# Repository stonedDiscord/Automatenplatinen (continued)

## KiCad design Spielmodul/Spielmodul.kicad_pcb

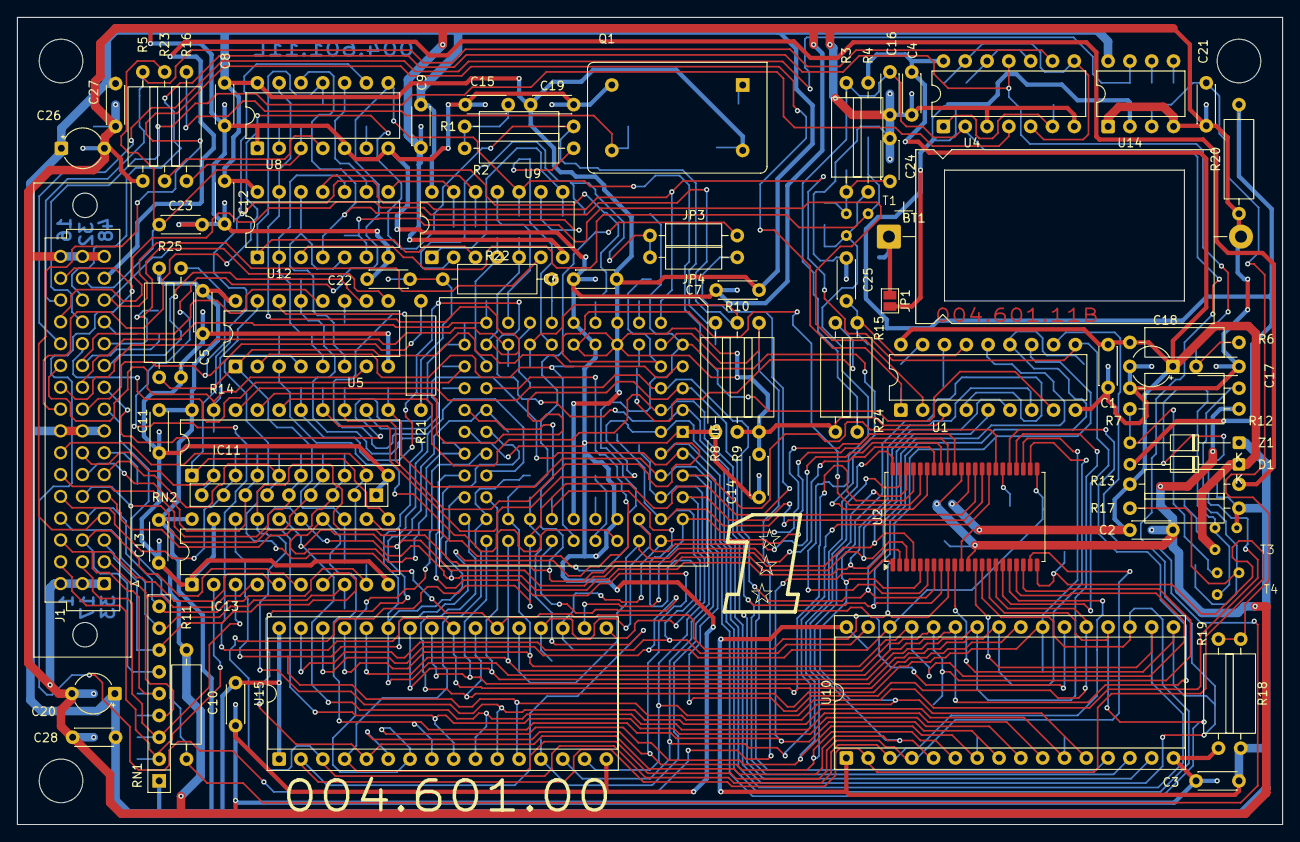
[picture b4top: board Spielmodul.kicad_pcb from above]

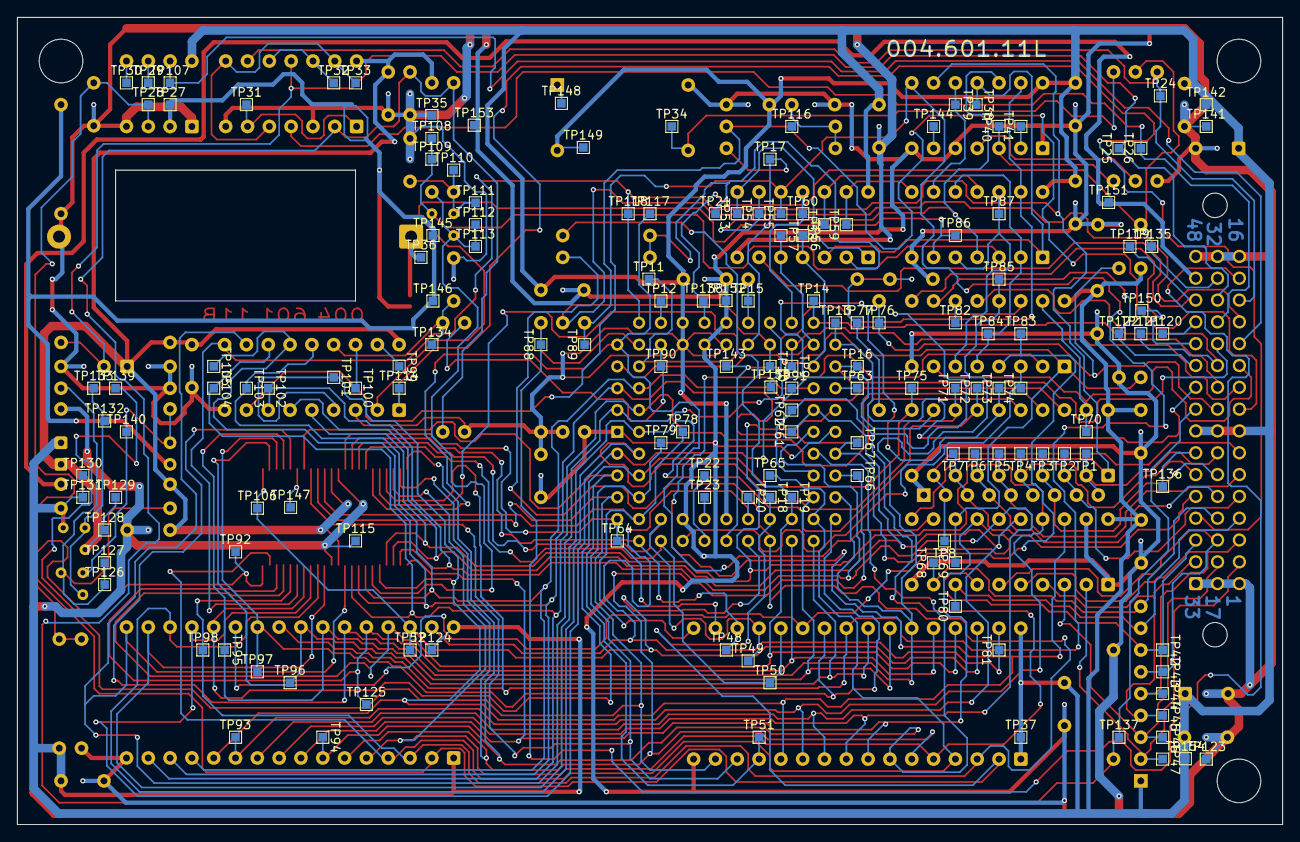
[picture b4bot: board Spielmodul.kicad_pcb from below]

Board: 2 copper layers, 147.3 x 94.0 mm, 234 parts (155 on the bottom side), 130 nets.

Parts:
BT1: Battery_Cell; CP_Axial_L34.5mm_D20.0mm_P41.00mm_Horizontal
C1, C2, C3, C4, C5, C6, C7, C8, C9, C10, C11, C12, C13, C14, C19, C21, C27, C28: 104M; C_Disc_D4.3mm_W1.9mm_P5.00mm
C15, C16, C22, C25: 470K; C_Disc_D4.3mm_W1.9mm_P5.00mm
C17: 103; C_Disc_D4.3mm_W1.9mm_P5.00mm
C18: 2u2 35; CP_Radial_Tantal_D4.5mm_P5.00mm
C20, C26: 10u 16; CP_Radial_Tantal_D4.5mm_P5.00mm
C23, C24: C; C_Disc_D4.3mm_W1.9mm_P5.00mm
D1: D; D_DO-34_SOD68_P12.70mm_Horizontal
IC11, IC13: 74HC245; DIP-20_W7.62mm
J1: DIN41612_03x16_ABC; DIN41612_R2_3x16_Male_Vertical_THT
JP1: Jumper_2_Open; SolderJumper-2_P1.3mm_Open_Pad1.0x1.5mm
JP3: Jumper_2_Bridged; R_Axial_DIN0207_L6.3mm_D2.5mm_P10.16mm_Horizontal
JP4: Jumper_2_Open; R_Axial_DIN0207_L6.3mm_D2.5mm_P10.16mm_Horizontal
Q1: ACO-xxxMHz; Oscillator_DIP-14
R1, R2, R7, R16, R21, R22, R23, R24: 100; R_Axial_DIN0309_L9.0mm_D3.2mm_P12.70mm_Horizontal
R3: 330; R_Axial_DIN0309_L9.0mm_D3.2mm_P12.70mm_Horizontal
R4, R15: 1k; R_Axial_DIN0309_L9.0mm_D3.2mm_P12.70mm_Horizontal
R5, R8, R13, R14, R25: 47k; R_Axial_DIN0309_L9.0mm_D3.2mm_P12.70mm_Horizontal
R6: 2.2M; R_Axial_DIN0309_L9.0mm_D3.2mm_P12.70mm_Horizontal
R9, R11: 10k; R_Axial_DIN0309_L9.0mm_D3.2mm_P12.70mm_Horizontal
R10: 4,7k; R_Axial_DIN0309_L9.0mm_D3.2mm_P12.70mm_Horizontal
R12: 47; R_Axial_DIN0309_L9.0mm_D3.2mm_P12.70mm_Horizontal
R17: 470; R_Axial_DIN0309_L9.0mm_D3.2mm_P12.70mm_Horizontal
R18: 56k; R_Axial_DIN0309_L9.0mm_D3.2mm_P12.70mm_Horizontal
R19: 39k; R_Axial_DIN0309_L9.0mm_D3.2mm_P12.70mm_Horizontal
R20: 10M; R_Axial_DIN0309_L9.0mm_D3.2mm_P12.70mm_Horizontal
RN1, RN2: R_Network08; R_Array_SIP9
T1: BS170; TO92
T3: BC557; TO92
T4: BC546; TO92
TP1, TP2, TP3, TP4, TP5, TP6, TP7, TP8: TestPoint; TestPoint_Pad_1.0x1.0mm
TP9: IPL2; TestPoint_Pad_1.0x1.0mm
TP10: VPA; TestPoint_Pad_1.0x1.0mm
TP11: UDS; TestPoint_Pad_1.0x1.0mm
TP12: BG; TestPoint_Pad_1.0x1.0mm
TP13: IPL0; TestPoint_Pad_1.0x1.0mm
TP14: IPL1; TestPoint_Pad_1.0x1.0mm
TP15, TP77: HALT; TestPoint_Pad_1.0x1.0mm
TP16, TP18, TP19, TP20, TP22, TP23, TP31, TP32, TP33, TP35, TP37, TP38, TP39, TP40, TP41, TP42, TP43, TP44, TP45, TP46, TP47, TP48, TP49, TP50, TP51, TP52, TP53, TP54, TP55, TP56, TP57, TP58, TP59, TP60, TP61, TP62, TP63, TP64, TP65, TP66, TP67, TP68, TP69, TP70, TP71, TP72, TP73, TP74, TP75, TP76, TP78, TP79, TP80, TP81, TP82, TP83, TP84, TP85, TP86, TP87, TP88, TP89, TP91, TP92, TP93, TP94, TP95, TP96, TP97, TP98, TP99, TP100, TP101, TP102, TP103, TP104, TP105, TP106, TP107, TP108, TP109, TP110, TP111, TP112, TP113, TP114, TP115, TP119, TP134, TP135, TP139, TP140, TP143, TP144, TP145, TP146, TP147, TP155: TestPoint_Pad_1.0x1.0mm
TP17, TP116: RESET; TestPoint_Pad_1.0x1.0mm
TP21: TP; TestPoint_Pad_1.0x1.0mm
TP24: c_c14; TestPoint_Pad_1.0x1.0mm
TP25: c_b14; TestPoint_Pad_1.0x1.0mm
TP26, TP120, TP121, TP122, TP123, TP124, TP125, TP126, TP127, TP128, TP129, TP130, TP131, TP132, TP133, TP136, TP137, TP141, TP142, TP148, TP149, TP150, TP151, TP152, TP153, TP154: c_b13; TestPoint_Pad_1.0x1.0mm
TP27: +BATT; TestPoint_Pad_1.0x1.0mm
TP28: MINUS; TestPoint_Pad_1.0x1.0mm
TP29: STRB; TestPoint_Pad_1.0x1.0mm
TP30: BAL; TestPoint_Pad_1.0x1.0mm
TP34: CLOCK_OUT; TestPoint_Pad_1.0x1.0mm
TP36: BT+; TestPoint_Pad_1.0x1.0mm
TP90: BGACK; TestPoint_Pad_1.0x1.0mm
TP117: LDS; TestPoint_Pad_1.0x1.0mm
TP118: RW; TestPoint_Pad_1.0x1.0mm
TP138: CLK; TestPoint_Pad_1.0x1.0mm
U1: RTC72421; DIP-18_W7.62mm
U2: K6T4016C3C; TSOP-II-44_10.16x18.41mm_P0.8mm
U4: 74HC02; DIP-14_W7.62mm
U5: 74HC139; DIP-16_W7.62mm
U6: MC68EC000FN16; PLCC-68_THT-Socket
U8: 74HC14; DIP-14_W7.62mm
U9: 74HC08; DIP-14_W7.62mm
U10, U15: 27C040; DIP-32_W15.24mm_Socket
U12: 74HC32; DIP-14_W7.62mm
U14: LM311; DIP-8_W7.62mm
Z1: D_Zener; D_DO-34_SOD68_P12.70mm_Horizontal

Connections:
+BATT: D1.2 (A), JP1.2 (B), R20.2, TP27.1 (1_1), TP145.1 (1_1), TP146.1 (1_1), U14.2 (+)
/cA1: IC13.2 (A0), J1.c2, RN1.2 (R1), TP47.1 (1_1)
/cA2: IC13.3 (A1), J1.b2, RN1.3 (R2), TP46.1 (1_1)
/cA3: IC13.4 (A2), J1.a2, RN1.4 (R3), TP45.1 (1_1)
/cA4: IC13.5 (A3), J1.c3, RN1.5 (R4), TP44.1 (1_1)
/cA5: IC13.6 (A4), J1.b3, RN1.6 (R5), TP43.1 (1_1)
/cAS: IC13.7 (A5), J1.a3, RN1.7 (R6), TP42.1 (1_1)
/cD0: IC11.2 (A0), J1.b7, RN2.9 (R8), TP1.1 (1_1)
/cD1: IC11.3 (A1), J1.c5, RN2.8 (R7), TP2.1 (1_1)
/cD2: IC11.4 (A2), J1.b6, RN2.7 (R6), TP3.1 (1_1)
/cD3: IC11.5 (A3), J1.a6, RN2.6 (R5), TP4.1 (1_1)
/cD4: IC11.6 (A4), J1.c6, RN2.5 (R4), TP5.1 (1_1)
/cD5: IC11.7 (A5), J1.b5, RN2.4 (R3), TP6.1 (1_1)
/cD6: IC11.8 (A6), J1.a5, RN2.3 (R2), TP7.1 (1_1)
/cD7: IC11.9 (A7), J1.c7, RN2.2 (R1), TP8.1 (1_1)
/cHALT: J1.b9, R14.2, R21.2, TP76.1 (1_1)
/cLDS: IC13.8 (A6), J1.c4, RN1.8 (R7), TP80.1 (1_1)
/cRAMVCC: J1.a15, R13.2, TP151.1 (1_1)
/cRESET: J1.c9, R1.2, R8.2, TP89.1 (1_1)
/cRW: IC13.9 (A7), J1.b4, RN1.9 (R8), TP68.1 (1_1)
/c_a4: J1.a4, TP114.1 (1_1), U1.1 (STD.P)
/c_a7: J1.a7, TP136.1 (1_1)
/c_a9: C16.1, J1.a9, R3.2, R11.1, R24.1, TP137.1 (1_1), U4.2
/c_a11: J1.a11, TP122.1 (1_1), U5.10 (O2)
/c_a12: J1.a12, TP150.1 (1_1), U5.9 (O3)
/c_a13: J1.a13, TP120.1 (1_1)
/c_b11: J1.b11, TP121.1 (1_1), U5.12 (O0)
/c_b13: J1.b13, TP26.1 (1_1), U4.4
/c_b14: C17.1, J1.b14, R6.2, TP25.1 (1_1), U4.11
/c_c12: J1.c12, TP107.1 (1_1), U14.7
/c_c14: J1.c14, R5.2, TP24.1 (1_1), U4.9
/c~USER: J1.a14, TP119.1 (1_1), U9.6
A0: TP63.1 (1_1), U6.31 (A0)
A1: IC13.18 (B0), TP101.1 (1_1), U1.4 (A0), U2.5 (A0), U6.32 (A1), U10.12 (A0), U15.12 (A0)
A2: IC13.17 (B1), TP93.1 (1_1), U1.5 (A1), U2.4 (A1), U6.33 (A2), U10.11 (A1), U15.11 (A1)
A3: IC13.16 (B2), TP61.1 (1_1), U1.6 (A2), U2.3 (A2), U6.34 (A3), U10.10 (A2), U15.10 (A2)
A4: IC13.15 (B3), TP102.1 (1_1), U1.7 (A3), U2.2 (A3), U6.36 (A4), U10.9 (A3), U15.9 (A3)
A5: IC13.14 (B4), TP67.1 (1_1), U2.1 (A4), U6.37 (A5), U10.8 (A4), U15.8 (A4)
A6: TP94.1 (1_1), U2.44 (A5), U6.38 (A6), U10.7 (A5), U15.7 (A5)
A7: TP66.1 (1_1), U2.43 (A6), U6.39 (A7), U10.6 (A6), U15.6 (A6)
A8: TP62.1 (1_1), U2.42 (A7), U5.14 (A0), U6.40 (A8), U10.5 (A7), U15.5 (A7)
A9: TP85.1 (1_1), U2.27 (A8), U5.13 (A1), U6.41 (A9), U10.27 (A8), U15.27 (A8)
A10: TP95.1 (1_1), U2.26 (A9), U6.42 (A10), U10.26 (A9), U15.26 (A9)
A11: TP97.1 (1_1), U2.25 (A10), U6.43 (A11), U10.23 (A10), U15.23 (A10)
A12: TP96.1 (1_1), U2.24 (A11), U6.44 (A12), U10.25 (A11), U15.25 (A11)
A13: TP65.1 (1_1), U2.21 (A14), U6.45 (A13), U10.4 (A12), U15.4 (A12)
A14: TP125.1 (1_1), U2.20 (A15), U6.46 (A14), U10.28 (A13), U15.28 (A13)
A15: JP3.2 (B), TP19.1 (1_1), U2.19 (A16), U6.47 (A15), U10.29 (A14), U15.29 (A14)
A16: JP4.2 (B), TP98.1 (1_1), U2.18 (A17), U6.48 (A16), U10.3 (A15), U15.3 (A15)
A17: TP18.1 (1_1), TP92.1 (1_1), U2.22 (A13), U6.49 (A17), U10.2 (A16), U15.2 (A16)
A18: TP52.1 (1_1), TP106.1 (1_1), U2.23 (A12), U6.50 (A18), U10.30 (A17), U15.30 (A17)
A19: TP20.1 (1_1), TP81.1 (1_1), U6.51 (A19), U10.31 (A18), U15.31 (A18)
A20: TP143.1 (1_1), U5.2 (A0), U6.52 (A20)
A21: TP22.1 (1_1), U6.54 (A21)
A22: TP23.1 (1_1), U6.55 (A22)
A23: TP74.1 (1_1), U5.3 (A1), U6.56 (A23)
AS: IC13.13 (B5), R25.1, TP69.1 (1_1), U5.1 (E), U6.7 (~AS)
CLK: C23.1, J1.b15, R23.2, TP135.1 (1_1), TP138.1 (1_1), U6.16 (CLK)
D0: IC11.18 (B0), TP103.1 (1_1), U1.14 (D0), U2.7 (I/O1), U6.6 (D0), U10.13 (D0)
D1: IC11.17 (B1), TP105.1 (1_1), U1.13 (D1), U2.8 (I/O2), U6.5 (D1), U10.14 (D1)
D2: IC11.16 (B2), TP104.1 (1_1), U1.12 (D2), U2.9 (I/O3), U6.4 (D2), U10.15 (D2)
D3: IC11.15 (B3), TP73.1 (1_1), U1.11 (D3), U2.10 (I/O4), U6.3 (D3), U10.17 (D3)
D4: IC11.14 (B4), TP72.1 (1_1), U2.13 (I/O5), U6.2 (D4), U10.18 (D4)
D5: IC11.13 (B5), TP71.1 (1_1), U2.14 (I/O6), U6.68 (D5), U10.19 (D5)
D6: IC11.12 (B6), TP91.1 (1_1), U2.15 (I/O7), U6.67 (D6), U10.20 (D6)
D7: IC11.11 (B7), TP75.1 (1_1), U2.16 (I/O8), U6.66 (D7), U10.21 (D7)
D8: TP51.1 (1_1), U2.29 (I/O9), U6.65 (D8), U15.13 (D0)
D9: TP79.1 (1_1), U2.30 (I/O10), U6.64 (D9), U15.14 (D1)
D10: TP139.1 (1_1), U2.31 (I/O11), U6.63 (D10), U15.15 (D2)
D11: TP78.1 (1_1), U2.32 (I/O12), U6.62 (D11), U15.17 (D3)
D12: TP64.1 (1_1), U2.35 (I/O13), U6.61 (D12), U15.18 (D4)
D13: TP48.1 (1_1), U2.36 (I/O14), U6.60 (D13), U15.19 (D5)
D14: TP49.1 (1_1), U2.37 (I/O15), U6.59 (D14), U15.20 (D6)
D15: TP50.1 (1_1), U2.38 (I/O16), U6.58 (D15), U15.21 (D7)
EXT_RANGE: IC11.19 (CE), J1.c11, TP70.1 (1_1), U5.7 (O3), U5.15 (E)
FC0: TP56.1 (1_1), U6.30 (FC0), U9.4
FC1: J1.b12, TP16.1 (1_1), U6.29 (FC1)
FC2: TP57.1 (1_1), U6.28 (FC2), U8.13, U9.5, U12.13
GND: BT1.2 (-), C1.2, C2.2, C3.2, C4.2, C5.2, C6.2, C7.2, C8.2, C9.2, C10.2, C11.2, C12.2, C13.2, C14.2, C15.2, C16.2, C17.2, C18.2, C19.2, C20.2, C21.2, C22.2, C23.2, C24.2, C25.2, C26.2, C27.2, C28.2, IC11.10 (GND), IC13.1 (A->B), IC13.10 (GND), IC13.19 (CE), J1.a1, J1.a16, J1.b1, J1.b16, J1.c1, J1.c16, Q1.7 (GND), R5.1, R7.2, R8.1, R11.2, R12.1, R14.1, R19.1, R20.1, RN2.1 (common), TP35.1 (1_1), TP115.1 (1_1), TP123.1 (1_1), TP141.1 (1_1), TP152.1 (1_1), TP153.1 (1_1), U1.9 (GND), U2.12 (Vss), U2.34 (Vss), U4.3, U4.7 (GND), U5.8 (GND), U6.1 (GND), U6.17 (GND), U6.18 (GND), U6.35 (GND), U6.57 (GND), U8.1, U8.5, U8.7 (GND), U9.7 (GND), U10.16 (GND), U12.7 (GND), U14.1 (GND), U14.4 (V-), U15.16 (GND)
IPL0: J1.a10, TP13.1 (1_1), U6.27 (~IPL0)
IPL1: J1.b10, TP14.1 (1_1), U6.26 (~IPL1)
IPL2: J1.c10, TP9.1 (1_1), U6.25 (~IPL2)
LDS: IC13.12 (B6), TP117.1 (1_1), U2.39 (~LB), U6.9 (~LDS)
unnamed: BT1.1 (+), JP1.1 (A), TP36.1 (1_1)
unnamed: C15.1, R1.1, R2.1, TP116.1 (1_1)
unnamed: C22.1, R21.1, R22.1, TP77.1 (1_1)
unnamed: JP3.1 (A), JP4.1 (A), TP21.1 (1_1), U9.2
unnamed: Q1.8 (OUT), R16.2, TP34.1 (1_1)
unnamed: R16.1, TP40.1 (1_1), U8.3
unnamed: R23.1, U8.4
unnamed: R4.1, T1.1 (D), TP112.1 (1_1), TP113.1 (1_1), U2.6 (~CS)
unnamed: C24.1, R3.1, T1.2 (G), TP110.1 (1_1), TP111.1 (1_1)
unnamed: T3.2 (B), T4.1 (C), TP132.1 (1_1), TP133.1 (1_1)
unnamed: R7.1, T4.2 (B), TP140.1 (1_1), Z1.2 (A)
unnamed: R12.2, R17.1, T4.3 (E), TP126.1 (1_1), TP127.1 (1_1)
unnamed: TP31.1 (1_1), U4.1, U4.6
unnamed: TP32.1 (1_1), U4.10, U4.12
unnamed: TP33.1 (1_1), U4.5, U4.8, U4.13
unnamed: TP38.1 (1_1), U8.11, U9.3, U12.1
unnamed: TP39.1 (1_1), U8.10, U12.9
unnamed: TP41.1 (1_1), U8.2
unnamed: TP53.1 (1_1), U9.1, U9.8
unnamed: TP54.1 (1_1), U8.12, U9.9, U12.4
unnamed: TP58.1 (1_1), U9.12, U12.11
unnamed: TP59.1 (1_1), U9.13, U12.8
unnamed: TP99.1 (1_1), U1.17 (Vdd)
unnamed: TP100.1 (1_1), U1.16 (Vdd)
unnamed: TP144.1 (1_1), U8.6
unnamed: C25.1, R24.2, TP134.1 (1_1), U1.15 (CS1)
unnamed: TP82.1 (1_1), U5.11 (O1)
unnamed: C21.1, R18.2, R19.2, TP28.1 (1_1), U14.3 (-)
unnamed: TP30.1 (1_1), U14.5 (BAL)
unnamed: TP29.1 (1_1), U14.6 (STRB)
OE: TP55.1 (1_1), U1.8 (~RD), U2.41 (~OE), U8.8, U9.10, U10.24 (~OE), U15.24 (~OE)
RAMVCC: C1.1, C2.1, C4.1, C18.1, D1.1 (K), R4.2, R6.1, R13.1, T3.1 (C), TP128.1 (1_1), TP129.1 (1_1), U1.18 (Vdd), U2.11 (Vcc), U2.33 (Vcc), U4.14 (VCC)
RAM_RANGE: TP84.1 (1_1), U5.5 (O1), U12.2, U12.10
RAM_SELECT: T1.3 (S), TP108.1 (1_1), TP109.1 (1_1), U12.3
ROM_CE: TP83.1 (1_1), U5.4 (O0), U10.22 (~CE), U15.22 (~CE)
RTC_CS: TP86.1 (1_1), U1.2 (~CS0), U12.6
RTC_RANGE: TP87.1 (1_1), U5.6 (O2), U12.5, U12.12
R/~W: IC11.1 (A->B), IC13.11 (B7), TP118.1 (1_1), U1.10 (~WR), U2.17 (~WE), U6.10 (R/~W), U8.9
UDS: TP11.1 (1_1), U2.40 (~UB), U6.8 (~UDS)
VCC: C3.1, C5.1, C6.1, C7.1, C8.1, C9.1, C10.1, C11.1, C12.1, C13.1, C14.1, C19.1, C20.1, C26.1, C27.1, C28.1, IC11.20 (VCC), IC13.20 (VCC), J1.a8, J1.b8, J1.c8, Q1.14 (Vcc), R9.1, R10.1, R15.1, R17.2, R18.1, R25.2, RN1.1 (common), T3.3 (E), TP37.1 (1_1), TP124.1 (1_1), TP130.1 (1_1), TP131.1 (1_1), TP142.1 (1_1), TP149.1 (1_1), TP154.1 (1_1), U1.3 (ALE), U5.16 (VCC), U6.14 (~BR), U6.15 (V_{CC}), U6.19 (MODE), U6.53 (V_{CC}), U8.14 (VCC), U9.14 (VCC), U10.1 (VPP), U10.32 (VCC), U12.14 (VCC), U14.8 (V+), U15.1 (VPP), U15.32 (VCC), Z1.1 (K)
~AVEC: J1.c13, R9.2, TP10.1 (1_1), U6.23 (~AVEC)
~BERR: TP60.1 (1_1), U6.24 (~BERR), U9.11
~BGACK: R15.2, TP90.1 (1_1), U6.13 (~BGACK)
~BG: TP12.1 (1_1), U6.12 (~BG)
~DTACK: J1.c15, R10.2, TP88.1 (1_1), U6.11 (~DTACK)
~HALT: R22.2, TP15.1 (1_1), U6.20 (~HALT)
~RESET: R2.2, TP17.1 (1_1), U6.21 (~RESET)

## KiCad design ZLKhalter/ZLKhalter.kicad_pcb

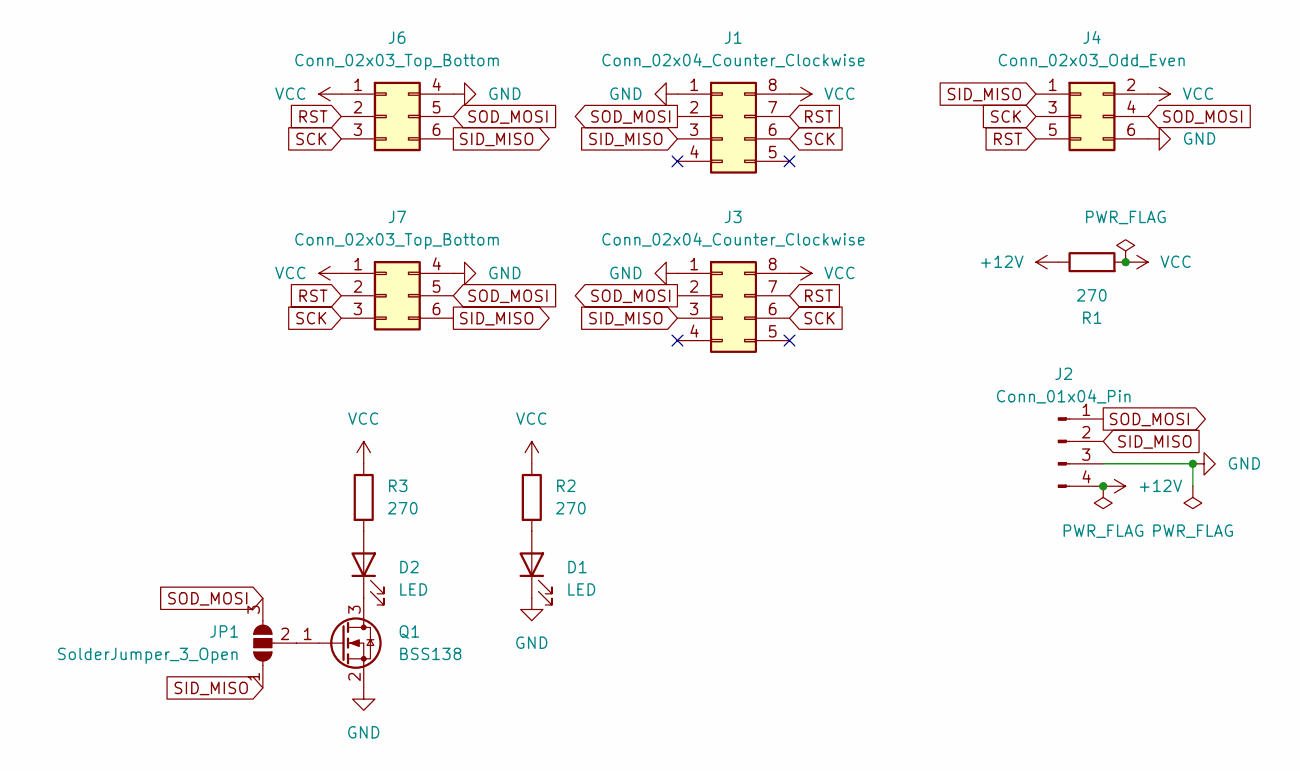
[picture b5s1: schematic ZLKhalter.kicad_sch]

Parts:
D1, D2: LED; LED_0805_2012Metric_Pad1.15x1.40mm_HandSolder
J1, J3: Conn_02x04_Counter_Clockwise; SIMsocket
J2: Conn_01x04_Pin; JST_XH_S4B-XH-A-1_1x04_P2.50mm_Horizontal
J4: Conn_02x03_Odd_Even; IDC-Header_2x03_P2.54mm_Vertical
J6, J7: Conn_02x03_Top_Bottom; 4FF-SIM
JP1: SolderJumper_3_Open; SolderJumper-3_P1.3mm_Open_Pad1.0x1.5mm
Q1: BSS138; SOT-23
R1, R2, R3: 270; R_0805_2012Metric_Pad1.20x1.40mm_HandSolder

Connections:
+12V: J2.4, R1.1
GND: D1.1 (K), J1.1, J2.3, J3.1, J4.6, J6.4, J7.4, Q1.2 (S)
unnamed: D1.2 (A), R2.2
unnamed: D2.2 (A), R3.2
unnamed: D2.1 (K), Q1.3 (D)
unnamed: JP1.2 (C), Q1.1 (G)
RST: J1.7, J3.7, J4.5, J6.2, J7.2
SCK: J1.6, J3.6, J4.3, J6.3, J7.3
SID_MISO: J1.3, J2.2, J3.3, J4.1, J6.6, J7.6, JP1.1 (A)
SOD_MOSI: J1.2, J2.1, J3.2, J4.4, J6.5, J7.5, JP1.3 (B)
VCC: J1.8, J3.8, J4.2, J6.1, J7.1, R1.2, R2.1, R3.1

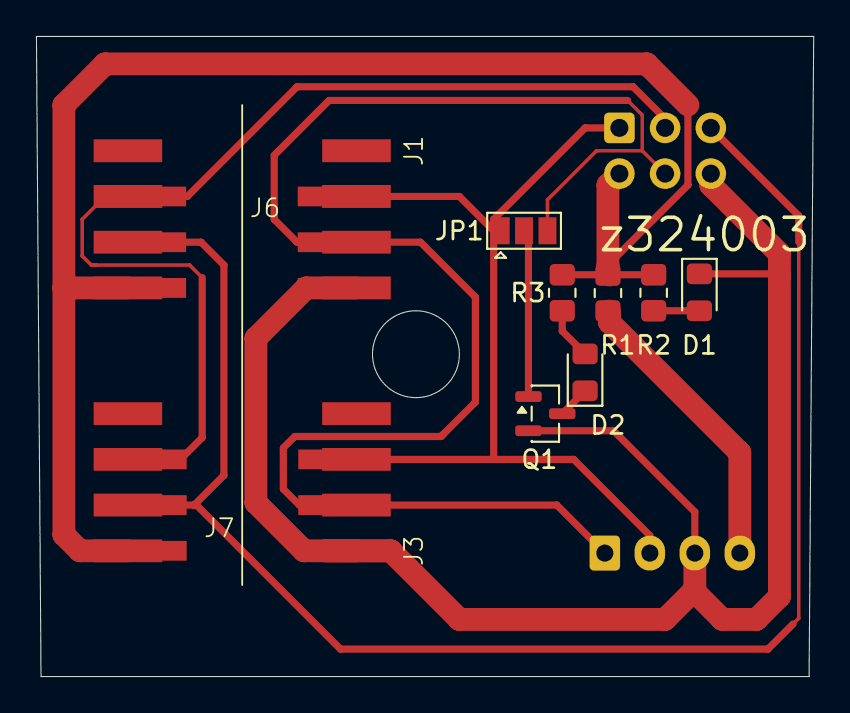
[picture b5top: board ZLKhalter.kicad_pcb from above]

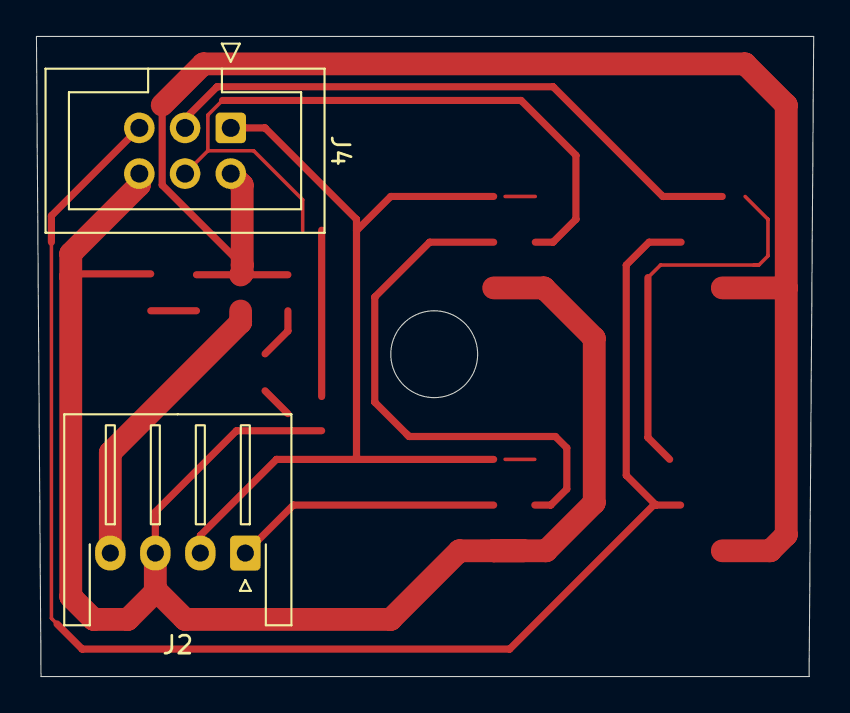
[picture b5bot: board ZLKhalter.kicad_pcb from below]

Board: 2 copper layers, 43.2 x 35.6 mm, 13 parts (2 on the bottom side), 11 nets.

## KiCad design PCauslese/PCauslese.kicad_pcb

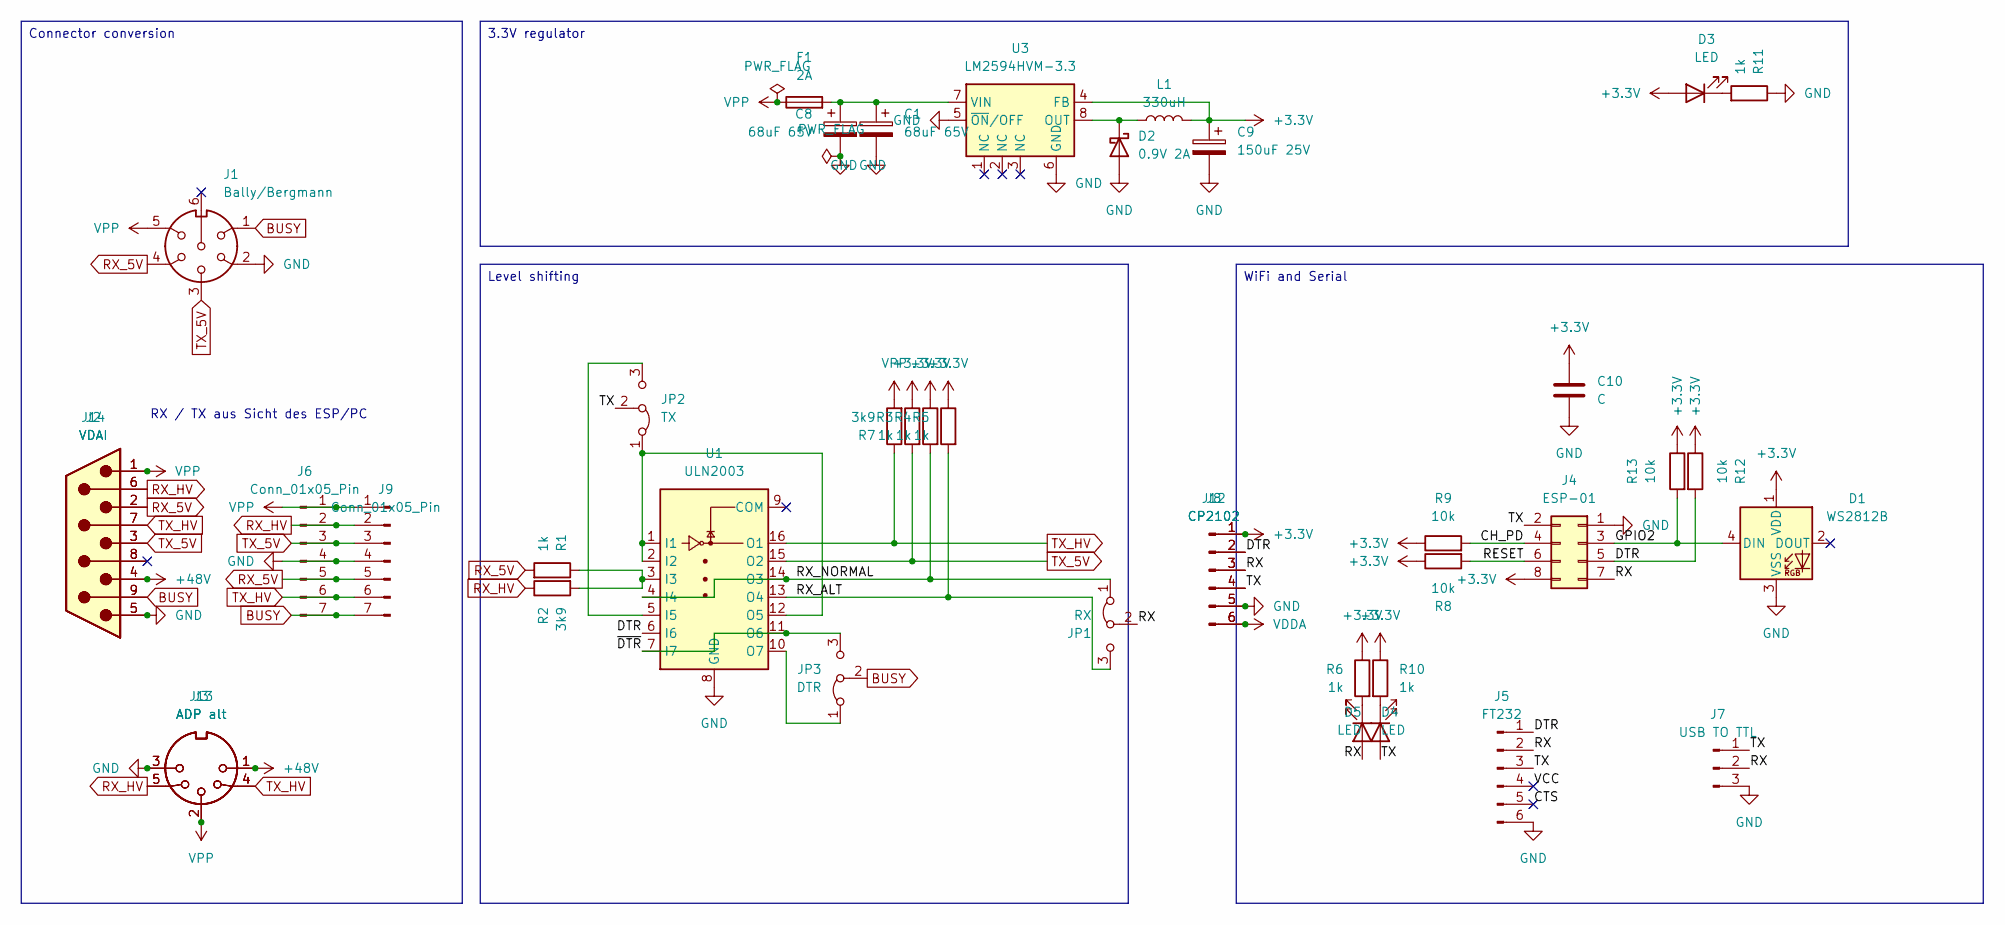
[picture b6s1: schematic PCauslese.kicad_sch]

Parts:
C1: 68uF 65V; CP_Elec_5x5.7
C8: 68uF 65V; CP_EIA-6032-28_Kemet-C
C9: 150uF 25V; CP_Elec_6.3x5.4
C10: C; C_0603_1608Metric
D1: WS2812B; LED_WS2812B_PLCC4_5.0x5.0mm_P3.2mm
D2: 0.9V 2A; D_SOD-123
D3, D4, D5: LED; LED_0603_1608Metric
F1: 2A; Fuse_0805_2012Metric
J1: Bally/Bergmann; DIN45322
J2: VDAI; DSUB-9_Pins_EdgeMount_P2.77mm
J3: ADP alt; DIN41524
J4: ESP-01; PinSocket_2x04_P2.54mm_Vertical
J5: FT232; PinSocket_1x06_P2.54mm_Vertical
J6, J9: Conn_01x05_Pin; PinHeader_1x07_P2.54mm_Vertical
J7: USB TO TTL; PinSocket_1x03_P2.54mm_Vertical
J8, J12: CP2102; PinHeader_1x06_P2.54mm_Vertical
J13: ADP alt; DIN41524edge
J14: VDAI; DSUB-9_Pins_Vertical_P2.77x2.84mm
JP1: RX; PinHeader_1x03_P2.54mm_Vertical
JP2: TX; PinHeader_1x03_P2.54mm_Vertical
JP3: DTR; PinHeader_1x03_P2.54mm_Vertical
L1: 330uH; L_APV_ANR6045
R1, R3, R4, R5, R6, R10, R11: 1k; R_0603_1608Metric
R2, R7: 3k9; R_0603_1608Metric
R8, R9, R12, R13: 10k; R_0603_1608Metric
U1: ULN2003; SO-16_3.9x9.9mm_P1.27mm
U3: LM2594HVM-3.3; SOIC-8_3.9x4.9mm_P1.27mm

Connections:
+3.3V: C9.1, C10.1, D1.1 (VDD), D3.2 (A), J4.8, J8.1, J12.1, L1.2, R3.1, R4.1, R5.1, R6.1, R8.1, R9.1, R10.1, R12.1, R13.1, U3.4 (FB)
+48V: J2.4, J3.1, J13.1, J14.4
/CH_PD: J4.4, R9.2
/CTS: J5.5
/DTR: J4.5, J5.1, J8.2, J12.2, R12.2, U1.6 (I6)
/GPIO2: D1.4 (DIN), J4.3, R13.2
/RESET: J4.6, R8.2
/RX: D4.2 (A), J4.7, J5.2, J7.2, J8.3, J12.3, JP1.2 (C)
/RX_ALT: JP1.3 (B), R5.2, U1.13 (O4)
/RX_NORMAL: JP1.1 (A), R4.2, U1.4 (I4), U1.14 (O3)
/TX: D5.2 (A), J4.2, J5.3, J7.1, J8.4, J12.4, JP2.2 (C)
/VCC: J5.4
/~DTR: JP3.3 (B), U1.7 (I7), U1.11 (O6)
BUSY: J1.1, J2.9, J6.7, J9.7, J14.9, JP3.2 (C)
GND: C1.2, C8.2, C9.2, C10.2, D1.3 (VSS), D2.2 (A), J1.2, J2.5, J3.3, J4.1, J5.6, J6.4, J7.3, J8.5, J9.4, J12.5, J13.3, J14.5, R11.1, U1.8 (GND), U3.5 (~ON/OFF), U3.6 (GND)
unnamed: D2.1 (K), L1.1, U3.8 (OUT)
unnamed: D3.1 (K), R11.2
unnamed: D4.1 (K), R6.2
unnamed: D5.1 (K), R10.2
unnamed: JP2.1 (A), U1.1 (I1), U1.2 (I2), U1.12 (O5)
unnamed: JP2.3 (B), U1.5 (I5)
unnamed: JP3.1 (A), U1.10 (O7)
unnamed: R1.1, R2.2, U1.3 (I3)
unnamed: C1.1, C8.1, F1.2, U3.7 (VIN)
RX_5V: J1.4, J2.2, J6.5, J9.5, J14.2, R1.2
RX_HV: J2.6, J3.5, J6.2, J9.2, J13.5, J14.6, R2.1
TX_5V: J1.3, J2.3, J6.3, J9.3, J14.3, R3.2, U1.15 (O2)
TX_HV: J2.7, J3.4, J6.6, J9.6, J13.4, J14.7, R7.1, U1.16 (O1)
VDDA: J8.6, J12.6
VPP: F1.1, J1.5, J2.1, J3.2, J6.1, J9.1, J13.2, J14.1, R7.2

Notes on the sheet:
RX / TX aus Sicht des ESP/PC
WiFi and Serial
Level shifting
Connector conversion
3.3V regulator

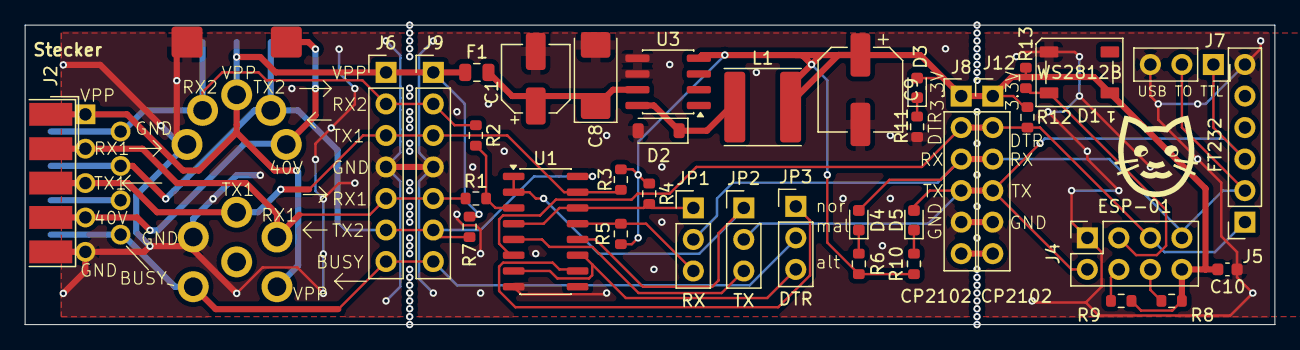
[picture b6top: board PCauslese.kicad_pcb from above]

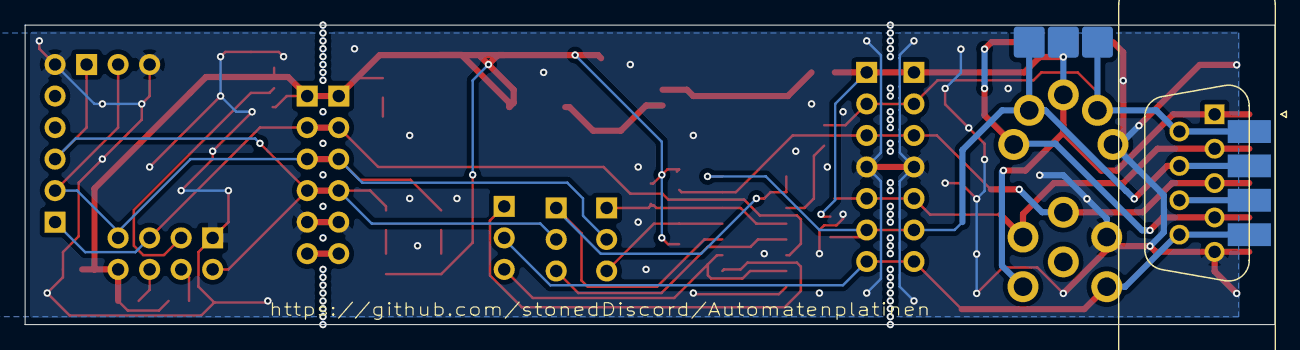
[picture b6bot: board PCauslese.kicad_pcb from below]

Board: 2 copper layers, 100.7 x 24.1 mm, 41 parts (3 on the bottom side), 28 nets.
